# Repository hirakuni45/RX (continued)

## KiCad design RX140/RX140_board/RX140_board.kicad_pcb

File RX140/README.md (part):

## RX140 features / 特徴

- RXv2 core / RXv2 コア
- Maximum operating frequency 48MHz / 最大動作周波数 48MHz
- Single-precision 32-bit floating point / 32 ビット単精度浮動小数点
- 1.8V ～ 5.5V Operation / 動作
- RSCAN CAN Module / RSCAN CAN モジュール
- 12 Bits A/D / １２ビットＡ／Ｄ変換器
- 8 Bits D/A / ８ビットＤ／Ａ変換器

### Package/パッケージ

|R5F5140---XX|Package/パッケージ|Pin/ピン数|Pitch/ピッチ|
|---|:-:|:-:|:-:|
|R5F5140xxxFN|LFQFP|80|0.50|
|R5F5140xxxFM|LFQFP|64|0.50|
|R5F5140xxxFK|LQFP|64|0.80|
|R5F5140xxxFL|LFQFP|48|0.50|
|R5F5140xxxNE|HWQFN|48|0.50|
|R5F5140xxxFJ|LFQFP|32|0.80|
|R5F5140xxxNH|HWQFN|32|0.50|

### Ambient operating temperature/動作周囲温度

|R5F5140--X--|degree Celsius|
|---|:-:|
|R5F5140xxDxx|-40 ～ +85℃|
|R5F5140xxGxx|-40 ～ +105℃|

### Crypt/暗号

|R5F5140-X---|Crypt|
|---|:-:|
|R5F5140xAxxx|-|
|R5F5140xBxxx|〇|

### Memoey size/メモリ容量

|R5F5140X----|CodeFlash|RAM|DataFlash|
|---|:-:|:-:|:-:|
|R5F51406xxxx|256K|64K|8K|
|R5F51405xxxx|128K|32K|8K|
|R5F51403xxxx|64K|16K|4K|

### Data Flash/データ・フラッシュ

|Capacity|Erase Size|Blank Check Size|Write Size|Erase Value|ID|
|:-:|:-:|:-:|:-:|:-:|:-:|
|4K/8K|256|1/256|1|0xFF|4|

---

## RX140 Linker file / リンカーファイル

|Type|Code Flash|RAM|Data Flash|Linker File|Ustack|Istack|
|---|:-:|:-:|:-:|---|:-:|:-:|
|R5F51406|256K|64K|8K|[R5F51406.ld](R5F51406.ld?ts=4)|3072|1024|
|R5F51405|128K|32K|8K|[R5F51405.ld](R5F51405.ld?ts=4)|1536|512|
|R5F51403|64K|16K|4K|[R5F51403.ld](R5F51403.ld?ts=4)|768|256|

---

## RX140 Dedicated class / 専用クラス

|Function/機能|Source|Remarks/備考|
|---|---|:-:|
|Peripheral Name/ペリフェラル名|[peripheral.hpp](peripheral.hpp?ts=4)||
|Hardware-specific Definition/ハード固有定義|[board_profile.hpp](board_profile.hpp?ts=4)||
|Operating Frequency Definition/動作周波数定義|[clock_profile.hpp](clock_profile.hpp?ts=4)||
|Power Control/電力制御|[power_mgr.hpp](power_mgr.hpp?ts=4)||
|Port Definition/ポート定義|[port.hpp](port.hpp?ts=4)||
|Interrupt Definition/割り込み定義|[icu.hpp](icu.hpp?ts=4)||
|Interrupt Management/割り込み管理|[icu_mgr.hpp](icu_mgr.hpp?ts=4)||
|Port Function Definition/ポート機能定義|[mpc.hpp](mpc.hpp?ts=4)||
|Port Mapping/ポートマッピング|[port_map.hpp](port_map.hpp?ts=4)||
|Port Mapping IRQ/ポートマッピング IRQ|[port_map_irq.hpp](port_map_irq.hpp?ts=4)||
|Port Mapping MTU/ポートマッピング MTU|[port_map_mtu.hpp](port_map_mtu.hpp?ts=4)||
|Port Mapping MTU/ポートマッピング TMR|[port_map_tmr.hpp](port_map_tmr.hpp?ts=4)||
|A/D Definition/A/D 定義|[RX231/s12ade.hpp](../RX231/s12ade.hpp?ts=4)||
|D/A Definition/D/A 定義|[da.hpp](da.hpp?ts=4)||
|BUS Definition/BUS 定義|[bus.hpp](bus.hpp?ts=4)||
|ELC Definition/ELC 定義|[elc.hpp](elc.hpp?ts=4)||
|RTC Definition/RTC 定義|[rtc.hpp](rtc.hpp?ts=4)||
|FLASH Definition/FLASH 定義|[flash.hpp](flash.hpp?ts=4)||
|FLASH I/O Definition/FLASH I/O 定義|[RX24T/flash_io.hpp](../RX24T/flash.hpp?ts=4)||
|System Definition/システム定義|[system.hpp](system.hpp?ts=4)||
|System I/O Definition/システム I/O 定義|[system_io.hpp](system_io.hpp?ts=4)||
|A/D I/O Definition/A/D I/O 定義|[RX24T/adc_io.hpp](../RX24T/adc_io.hpp?ts=4)||
|D/A out Definition/D/A out 定義|[RX600/dac_out.hpp](../RX600/adc_io.hpp?ts=4)||

---

## Basic Pin Assignments / 基本ピンアサイン

|Terminal/端子|LFQFP 64|LFQFP 80|
|---|---|---|
|VCL|VCL(2)|VCL(4)|
|Reset Input/リセット入力|RES#(6)|RES#(9)|
|Mode Controle/モード制御|MD/FINED(3)|MD/FINED(6)|
|RXD|P30/RXD1(14)|P30/RXD1(18)|
|TXD|P26/TXD1(16)|P26/TXD1(20)|
|Power/電源|VCC(10), VCC(38)|VCC(13), VCC(48)|
|GND/接地|VSS(8), VSS(40)|VSS(11), VSS(50)|
|Analog Power/アナログ電源|AVCC0(62)|AVCC0(77)|
|Analog GND/アナログ接地|AVSS0(64)|AVSS0(79)|
|Analog Refarence L/アナログ基準電源Ｌ|VREFL0(59)|VREFL0(74)|
|Analog Refarence H/アナログ基準電源Ｈ|VREFH0(61)|VREFH0(76)|
|OSC out|XTAL(7)|XTAL(10)|
|OSC in|EXTAL(9)|EXTAL(12)|
|Sub OSC out|XCOUT(5)|XCOUT(8)|
|Sub OSC in|XCIN(4)|XCIN(7)|

- VCL: 4.7uF/25V

|Mode/モード|MD|
|---|:---:|
|Serial BOOT/シリアルブート|0|
|Single Chip/シングルチップ|1|

---

## Peripheral / ペリフェラル

- [peripheral.hpp](peripheral.hpp?ts=4)

|Peripheral|Function|機能|
|---|---|---|
|CAC|Clock Frequency Accuracy Measurement Circuit|クロック周波数精度測定回路|
|DTC|Data Transfer Controller|データトランスファコントローラ|
|ELC|Event Link Controller|イベントリンクコントローラ|
|MTU0|Multi-Function Timer Pulse Unit 0|マルチファンクションタイマパルスユニット０|
|MTU1|Multi-Function Timer Pulse Unit 1|マルチファンクションタイマパルスユニット１|
|MTU2|Multi-Function Timer Pulse Unit 2|マルチファンクションタイマパルスユニット２|
|MTU3|Multi-Function Timer Pulse Unit 3|マルチファンクションタイマパルスユニット３|
|MTU4|Multi-Function Timer Pulse Unit 4|マルチファンクションタイマパルスユニット４|
|MTU5|Multi-Function Timer Pulse Unit 5|マルチファンクションタイマパルスユニット５|
|POE2|Port Output Enable 2|ポートアウトプットイネーブル２|
|TPU0|16-Bit Timer Pulse Unit 0|16 ビットタイマパルスユニット０|
|TPU1|16-Bit Timer Pulse Unit 1|16 ビットタイマパルスユニット１|
|TPU2|16-Bit Timer Pulse Unit 2|16 ビットタイマパルスユニット２|
|TPU3|16-Bit Timer Pulse Unit 3|16 ビットタイマパルスユニット３|
|TPU4|16-Bit Timer Pulse Unit 4|16 ビットタイマパルスユニット４|
|TPU5|16-Bit Timer Pulse Unit 5|16 ビットタイマパルスユニット５|
|TMR0|8-Bit Timer 0|8 ビットタイマ０|
|TMR1|8-Bit Timer 1|8 ビットタイマ１|
|TMR2|8-Bit Timer 2|8 ビットタイマ２|
|TMR3|8-Bit Timer 3|8 ビットタイマ３|
|CMT0|Compare Match Timer 0|コンペアマッチタイマ０|
|CMT1|Compare Match Timer 1|コンペアマッチタイマ１|
|RTC|Realtime Clock|リアルタイムクロック|
|LPT|Low Power Timer|ローパワータイマ|
|IWDT|Independent Watchdog Timer|独立ウォッチドッグタイマ|
|SCI1|Serial Communications Interface 1|シリアルコミュニケーションインタフェース１|
|SCI5|Serial Communications Interface 5|シリアルコミュニケーションインタフェース５|
|SCI6|Serial Communications Interface 6|シリアルコミュニケーションインタフェース６|
|SCI8|Serial Communications Interface 8|シリアルコミュニケーションインタフェース８|
|SCI9|Serial Communications Interface 9|シリアルコミュニケーションインタフェース９|
|SCI11|Serial Communications Interface 11|シリアルコミュニケーションインタフェース１１|
|SCI12|Serial Communications Interface 12|シリアルコミュニケーションインタフェース１２|
|RIIC0|I2C-bus Interface 0|I2C バスインタフェース０|
|RSCAN|RSCAN Module|RSCAN モジュール|
|RSPI0|Serial Peripheral Interface 0|シリアルペリフェラルインタフェース０|
|CRC|CRC Calculator|CRC 演算器|
|CTSU|Capacitive Touch Sensing Unit|静電容量式タッチセンサ|
|S12AD|12-Bit A/D Converter|12 ビット A/D コンバータ|
|DA|8-Bit D/A Converter|8 ビット D/A コンバータ|
|CMPB|Comparator B|コンパレータＢ|
|DOC|Data Operation Circuit|データ演算回路|

---

## Port map order (IRQ) / ポートマップ候補 (IRQ)

- [port_map_irq.hpp](port_map_irq.hpp?ts=4)

### LFQFP48

|IRQ|FIRST|SECOND|THIRD|FOURTH|
|---|---|---|---|---|
|IRQ0|P30 (10)|PD0 (--)|PH1 (19)|-|
|IRQ1|P31 (9)|PD1 (--)|PH2 (18)|-|
|IRQ2|P12 (--)|P32 (--)|P36 (6)|PD2 (--)|
|IRQ3|P13 (--)|-|-|-|
|IRQ4|P14 (16)|P34 (--)|P37 (4)|PB1 (27)|
|IRQ5|P15 (15)|PA4 (32)|PE5 (--)|-|
|IRQ6|P16 (14)|PA3 (33)|-|-|
|IRQ7|P17 (13)|PE2 (37)|-|-|

### LFQFP64

|IRQ|FIRST|SECOND|THIRD|FOURTH|
|---|---|---|---|---|
|IRQ0|P30 (14)|PD0 (--)|PH1 (23)|-|
|IRQ1|P31 (13)|PD1 (--)|PH2 (22)|-|
|IRQ2|P12 (--)|P32 (12)|P36 (9)|PD2 (--)|
|IRQ3|P13 (--)|-|-|-|
|IRQ4|P14 (20)|P34 (--)|P37 (7)|PB1 (37)|
|IRQ5|P15 (19)|PA4 (42)|PE5 (46)|-|
|IRQ6|P16 (18)|PA3 (43)|-|-|
|IRQ7|P17 (17)|PE2 (49)|-|-|

### LFQFP80

|IRQ|FIRST|SECOND|THIRD|FOURTH|
|---|---|---|---|---|
|IRQ0|P30 (18)|PD0 (66)|PH1 (31)|-|
|IRQ1|P31 (17)|PD1 (65)|PH2 (30)|-|
|IRQ2|P12 (28)|P32 (16)|P36 (12)|PD2 (64)|
|IRQ3|P13 (27)|-|-|-|
|IRQ4|P14 (26)|P34 (15)|P37 (10)|PB1 (47)|
|IRQ5|P15 (25)|PA4 (53)|PE5 (58)|-|
|IRQ6|P16 (24)|PA3 (54)|-|-|
|IRQ7|P17 (23)|PE2 (61)|-|-|

---

## Port map order / ポートマップ候補

- [port_map.hpp](port_map.hpp?ts=4)

### LFQFP48

|Peripheral|FIRST|SECOND|THIRD|
|---|---|---|---|
|SCI1 / RXD|P15 (15)|P30 (10)|-|
|SCI1 / TXD|P16 (14)|P26 (12)|-|
|SCI1 / SCK|P17 (13)|P27 (11)|-|
|SCI5 / RXD|PA2 (--)|PA3 (33)|PC2 (26)|
|SCI5 / TXD|PA4 (32)|PA4 (32)|PC3 (25)|
|SCI5 / SCK|PA1 (34)|PA1 (34)|PC4 (24)|
|SCI6 / RXD|PB0 (29)|PD1 (--)|-|
|SCI6 / TXD|PB1 (27)|PD0 (--)|-|
|SCI6 / SCK|PB3 (26)|PD2 (--)|-|
|SCI8 / RXD|PC6 (22)|-|-|
|SCI8 / TXD|PC7 (21)|-|-|
|SCI8 / SCK|PC5 (23)|-|-|
|SCI9 / RXD|PB6 (--)|-|-|
|SCI9 / TXD|PB7 (--)|-|-|
|SCI9 / SCK|PB5 (25)|-|-|
|SCI12 / RXD|PE2 (37)|-|-|
|SCI12 / TXD|PE1 (38)|-|-|
|SCI12 / SCK|PE0 (--)|-|-|
|RIIC0 / SCL|P16 (14)|P12 (--)|-|
|RIIC0 / SDA|P17 (13)|P13 (--)|-|
|RSCAN / CRX|P15 (15)|P55 (--)|-|
|RSCAN / CTX|P14 (16)|P54 (--)|-|
|RSPI0 / RSPCK|PA5 (--)|PB0 (29)|PC5 (23)|
|RSPI0 / MOSI|PA6 (31)|P16 (14)|PC6 (22)|
|RSPI0 / MISO|PA7 (21)|P17 (13)|PC7 (21)|
|RSPI0 / SSL0|PA4 (32)|PC4 (24)|-|
|RSPI0 / SSL1|PA0 (--)|-|-|
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
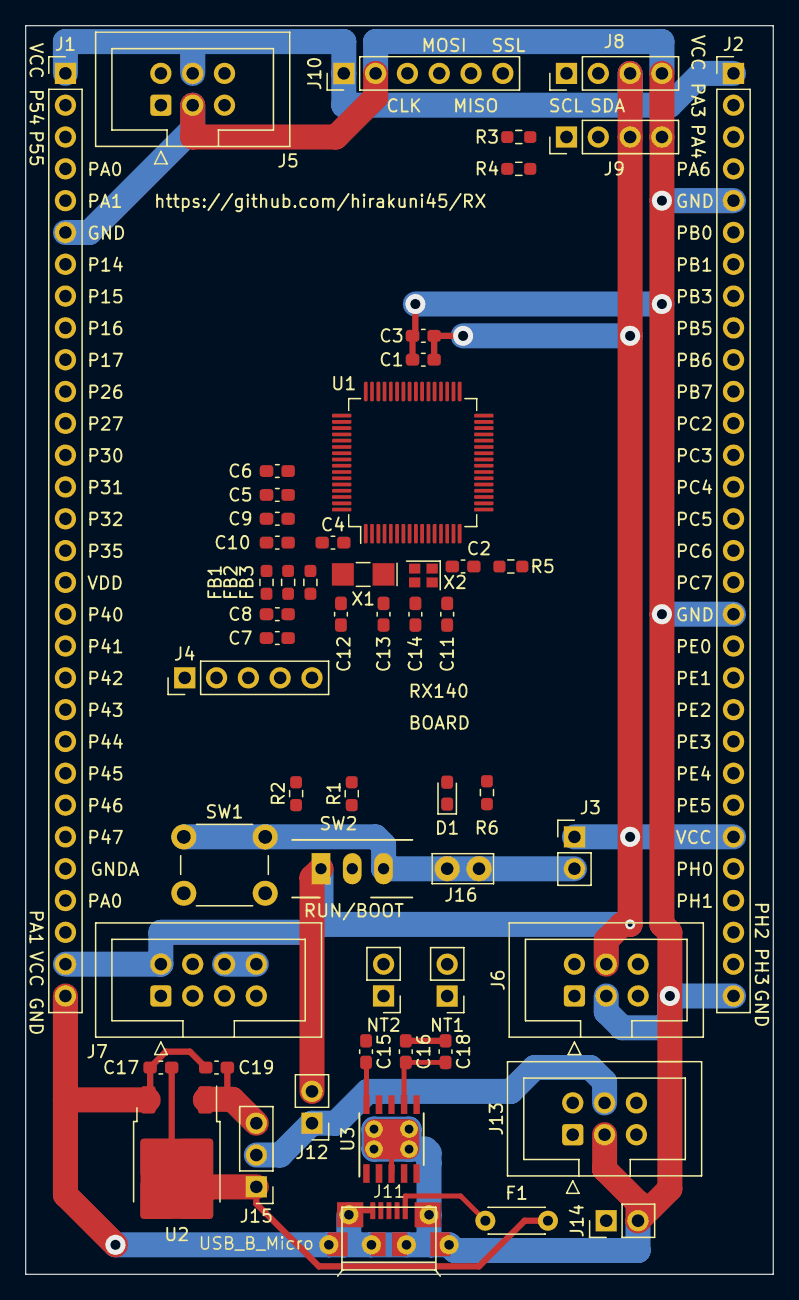
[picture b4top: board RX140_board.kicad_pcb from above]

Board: 2 copper layers, 59.7 x 99.7 mm, 55 parts (0 on the bottom side), 75 nets.

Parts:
C1, C2, C6, C7, C10, C15, C17, C18: 0.1uF; C_0603_1608Metric_Pad1.08x0.95mm_HandSolder
C3, C8, C16: 10uF; C_0603_1608Metric_Pad1.08x0.95mm_HandSolder
C4: 4.7uF; C_0603_1608Metric_Pad1.08x0.95mm_HandSolder
C5, C9: 0.01uF; C_0603_1608Metric_Pad1.08x0.95mm_HandSolder
C11, C14: 5pF; C_0603_1608Metric_Pad1.08x0.95mm_HandSolder
C12, C13: 10pF; C_0603_1608Metric_Pad1.08x0.95mm_HandSolder
C19: 1uF; C_0603_1608Metric_Pad1.08x0.95mm_HandSolder
D1: LED; LED_0603_1608Metric_Pad1.05x0.95mm_HandSolder
F1: MF-R050; C_Disc_D4.3mm_W1.9mm_P5.00mm
FB1, FB2, FB3: FB; R_0603_1608Metric_Pad0.98x0.95mm_HandSolder
J1: PIN-A; PinHeader_1x30_P2.54mm_Vertical
J2: PIN-B; PinHeader_1x30_P2.54mm_Vertical
J3: POWER; PinHeader_1x02_P2.54mm_Vertical
J4: D/A; PinHeader_1x05_P2.54mm_Vertical
J5: SCI12; IDC-Header_2x03_P2.54mm_Vertical
J6: SCI1; IDC-Header_2x03_P2.54mm_Vertical
J7: EMU; IDC-Header_2x04_P2.54mm_Vertical
J8: I2C-A; PinHeader_1x04_P2.54mm_Vertical
J9: I2C-B; PinHeader_1x04_P2.54mm_Vertical
J10: RSPI; PinHeader_1x06_P2.54mm_Vertical
J11: USB_B_Micro; USB_MICRO_B-HIROSE-ZX62R-B-5P
J12: 3.3V_CON; PinHeader_1x02_P2.54mm_Vertical
J13: Serial; IDC-Header_2x03_P2.54mm_Vertical
J14: /DTR; PinHeader_1x02_P2.54mm_Vertical
J15: 5/3.3; PinHeader_1x03_P2.54mm_Vertical
J16: GND; TestPoint_Bridge_Pitch2.54mm_Drill1.0mm
NT1: TIE_RXD; PinHeader_1x02_P2.54mm_Vertical
NT2: TIE_TXD; PinHeader_1x02_P2.54mm_Vertical
R1, R2, R5: 10K; R_0603_1608Metric_Pad0.98x0.95mm_HandSolder
R3, R4: 2K; R_0603_1608Metric_Pad0.98x0.95mm_HandSolder
R6: 1.5K; R_0603_1608Metric_Pad0.98x0.95mm_HandSolder
SW1: RES; SW_PUSH_6mm
SW2: RUN/BOOT; SW_3P_SPDT_Angled
U1: RX140; LQFP-64_10x10mm_P0.5mm
U2: NJU7223DL1-33; TO-252-2
U3: CH340K; SSOP-10_3.9x4.9mm_P1.00mm
X1: 32.768KHz; Crystal_SMD_EuroQuartz_EQ161-2Pin_3.2x1.5mm_HandSoldering
X2: 12MHz; Crystal_SMD_2016-4Pin_2.0x1.6mm

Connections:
/CH340 Serial USB/RXD: J13.1, NT2.1, U3.9 (RXD)
/CH340 Serial USB/TXD: J13.2, NT1.1, U3.8 (TXD)
DA0: J1.27, J4.2, U1.1 (P03)
DA1: J1.28, J4.3, U1.63 (P05)
GND: C1.1, C2.1, C3.2, C4.1, C7.1, C8.1, C11.1, C12.1, C13.1, C14.1, C15.1, C16.1, C17.1, C18.1, C19.1, FB1.1, J1.6, J1.30, J2.5, J2.18, J2.30, J3.2, J5.3, J6.3, J7.6, J7.8, J8.4, J9.4, J10.2, J11.5 (GND), J11.6 (Shield), J13.3, J14.2, J16.1, SW1.1, SW2.3, U1.8 (VSS), U1.40 (VSS), U2.3 (GND), U3.0 (GND), U3.3 (GND), X2.2, X2.4
GNDA: C5.2, C6.2, C9.1, C10.1, FB1.2, J1.26, J4.4, J4.5, U1.59 (VREFL0/PJ7), U1.64 (AVSS0)
LED: J1.8, R6.1, U1.19 (P15)
MISOA: J2.17, J10.5, U1.27 (PC7)
MOSIA: J2.16, J10.4, U1.28 (PC6)
NMI: J1.16, R5.1, U1.11 (P35)
unnamed: D1.1 (K), R6.2
unnamed: J7.1, R2.1, SW1.2, U1.6 (~RES)
unnamed: J7.3, R1.2, U1.3 (PG7/MD)
unnamed: J11.3 (D+), U3.1 (UD+)
unnamed: J11.2 (D-), U3.2 (UD-)
unnamed: F1.1, J11.1 (VBUS)
unnamed: J12.1, J13.4, J15.2
unnamed: J13.5, U3.6 (RTS#)
unnamed: J13.6, U3.5 (CTS#)
unnamed: J14.1, U3.4 (DTR#)
unnamed: C16.2, C17.2, C18.2, F1.2, J15.1, U2.2 (Vin), U3.7 (VCC)
unnamed: C19.2, J15.3, U2.1 (Vout)
unnamed: R1.1, SW2.2
unnamed: C11.2, U1.9 (P36/EXTAL), X2.1
unnamed: C14.2, U1.7 (P37/XTAL), X2.3
unnamed: C13.2, U1.5 (PH6/XCOUT), X1.1
unnamed: C12.2, U1.4 (PH7/XCIN), X1.2
unnamed: C4.2, U1.2 (VCL)
unnamed: C9.2, C10.2, FB3.1, U1.61 (VREFH0/PJ6)
unnamed: C15.2, U3.10 (V3)
P27: J1.12, U1.15 (P27)
P32: J1.15, U1.12 (P32)
P40: J1.18, U1.60 (P40)
P41: J1.19, U1.58 (P41)
P42: J1.20, U1.57 (P42)
P43: J1.21, U1.56 (P43)
P44: J1.22, U1.55 (P44)
P45: J1.23, U1.54 (P45)
P46: J1.24, U1.53 (P46)
P47: J1.25, U1.52 (P47)
P54: J1.2, U1.26 (P54)
P55: J1.3, U1.25 (P55)
PA0: J1.4, U1.45 (PA0)
PA1: J1.5, U1.44 (PA1)
PA3: J2.2, U1.43 (PA3)
PA4: J2.3, U1.42 (PA4)
PA6: J2.4, U1.41 (PA6)
PB0: J2.6, U1.39 (PB0)
PB1: J2.7, U1.37 (PB1)
PB3: J2.8, U1.36 (PB3)
PB5: J2.9, U1.35 (PB5)
PB6: J2.10, U1.34 (PB6/PC0)
PB7: J2.11, U1.33 (PB7/PC1)
PC2: J2.12, U1.32 (PC2)
PC3: J2.13, U1.31 (PC3)
PE0: J2.19, J5.6, U1.51 (PE0)
PE4: J2.23, U1.47 (PE4)
PE5: J2.24, U1.46 (PE5)
PH0: J2.26, U1.24 (PH0)
PH1: J2.27, U1.23 (PH1)
PH2: J2.28, U1.22 (PH2)
PH3: J2.29, U1.21 (PH3)
RSPCKA: J2.15, J10.3, U1.29 (PC5)
RXD1: J1.13, J6.2, J7.5, NT1.2, U1.14 (P30)
RXD12: J2.21, J5.2, U1.49 (PE2)
SCL0: J1.9, J8.1, J9.1, R3.2, U1.18 (P16)
SDA0: J1.10, J8.2, J9.2, R4.2, U1.17
SSLA0: J2.14, J10.6, U1.30 (PC4)
TXD1: J1.11, J6.1, J7.7, NT2.2, U1.16 (P26)
TXD12: J2.20, J5.1, U1.50 (PE1)
VCC: C1.2, C2.2, C3.1, C7.2, C8.2, D1.2 (A), FB2.2, FB3.2, J1.1, J1.29, J2.1, J2.25, J3.1, J5.4, J6.4, J7.2, J8.3, J9.3, J10.1, J12.2, R2.2, R3.1, R4.1, R5.2, SW2.1, U1.10 (VCC), U1.38 (VCC)
VDD: C5.1, C6.1, FB2.1, J1.17, J4.1, U1.62 (AVCC0)
/CTS1: J1.7, J6.5, U1.20 (P14)
/CTS12: J2.22, J5.5, U1.48 (PE3)
/RTS1: J1.14, J6.6, U1.13 (P31)

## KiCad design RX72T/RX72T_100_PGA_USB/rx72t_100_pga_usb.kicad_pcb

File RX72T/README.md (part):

## RX72T features / 特徴

- RXv3 core / RXv3 コア
- Maximum operating frequency 200MHz / 最大動作周波数 200MHz
- Single-precision 32-bit floating point / 32 ビット単精度浮動小数点
- 2.7V ～ 5.5V Operation / 動作
- USB2.0 Full Speed, Host, Function (Optional)
- CAN Module (CAN) / CAN モジュール (CAN)
- Arithmetic Unit for Trigonometric Functions (TFUv1) / 三角関数演算器 (TFUv1)
- 12 Bits A/D / １２ビットＡ／Ｄ変換器
- 12 Bits D/A / １２ビットＤ／Ａ変換器

### Package/パッケージ

|R5F572T---XX|Package/パッケージ|Pin/ピン数|Pitch/ピッチ|
|---|:-:|:-:|:-:|
|R5F572TxxxFB|LFQFP|144|0.50|
|R5F572TxxxFP|LFQFP|100|0.50|

### Ambient operating temperature/動作周囲温度

|R5F572T--X--|degree Celsius|
|---|:-:|
|R5F572TxxDxx|-40 ～ +85℃|
|R5F572TxxGxx|-40 ～ +105℃|

### PGA, TSIP, USB

|R5F572T-X---|PGA|TSIP|USB|
|---|:-:|:-:|:-:|
|R5F572TxAxxx|〇|-|-|
|R5F572TxBxxx|-|-|-|
|R5F572TxCxxx|〇|-|〇|
|R5F572TxExxx|〇|〇|-|
|R5F572TxFxxx|-|〇|-|
|R5F572TxGxxx|〇|〇|〇|

### Memoey size/メモリ容量

|R5F572TX----|CodeFlash|RAM|ECCRAM|DataFlash|
|---|:-:|:-:|:-:|:-:|
|R5F572TKxxxx|1M|128K|16K|32K|
|R5F572TFxxxx|512K|128K|16K|32K|

### Data Flash/データ・フラッシュ

|Capacity|Erase Size|Blank Check Size|Write Size|Erase Value|ID|
|:-:|:-:|:-:|:-:|:-:|:-:|
|32K|64|4/64|4|0x??|3|

---

## RX72T Linker file / リンカーファイル

|Type|Code Flash|RAM|Data Flash|Linker File|Ustack|Istack|
|---|:-:|:-:|:-:|---|:-:|:-:|
|R5F572TK|1024K|128K+16K|32K|[R5F572TK.ld](R5F572TK.ld?ts=4)|7168|1024|
|R5F572TF|512K|128K+16K|32K|[R5F572TF.ld](R5F572TF.ld?ts=4)|7168|1024|

RAM: 16K(With ECC)

---

## RX72T Dedicated class / 専用クラス

|Function/機能|Source|Remarks/備考|
|---|---|:-:|
|Peripheral Name/ペリフェラル名|[peripheral.hpp](peripheral.hpp?ts=4)||
|Hardware-specific Definition/ハード固有定義|[board_profile.hpp](board_profile.hpp?ts=4)||
|Operating Frequency Definition/動作周波数定義|[clock_profile.hpp](clock_profile.hpp?ts=4)||
|Power Control/電力制御|[power_mgr.hpp](power_mgr.hpp?ts=4)||
|Port Definition/ポート定義|[port.hpp](port.hpp?ts=4)||
|Interrupt Definition/割り込み定義|[icu.hpp](icu.hpp?ts=4)||
|Interrupt Management/割り込み管理|[icu_mgr.hpp](icu_mgr.hpp?ts=4)||
|Port Function Definition/ポート機能定義|[mpc.hpp](mpc.hpp?ts=4)||
|Port Mapping/ポートマッピング|[port_map.hpp](port_map.hpp?ts=4)||
|Port Mapping IRQ/ポートマッピング IRQ|[port_map_irq.hpp](port_map_irq.hpp?ts=4)||
|Port Mapping MTU/ポートマッピング MTU|[port_map_mtu.hpp](port_map_mtu.hpp?ts=4)||
|Port Mapping TMR/ポートマッピング TMR|[port_map_tmr.hpp](port_map_tmr.hpp?ts=4)||
|Port Mapping GPTW/ポートマッピング GPTW|[port_map_gptw.hpp](port_map_gptw.hpp?ts=4)||
|POE3 Definition/POE3 定義|[poe3.hpp](poe3.hpp?ts=4)||
|A/D Definition/A/D 定義|[s12adh.hpp](s12adh.hpp?ts=4)||

---

## Basic Pin Assignments / 基本ピンアサイン

|Terminal/端子|LFQFP 100|LFQFP 144|
|---|---|---|
|VCL|VCL(5)|VCL(10)|
|Reset Input/リセット入力|RES#(10)|RES#(15)|
|Mode Controle/モード制御|MD/FINED(6)|MD/FINED(11)|
|UB|P00/UB(4)|P00/UB(9)|
|EMLE|EMLE(2)|EMLE(7)|
|RXD|PD5/RXD1(20)|PD5/RXD1(25)|
|TXD|PD3/TXD1(22)|PD3/TXD1(27)|
|UPSEL|PE2/UPSEL(15)|PE2/UPSEL(20)|
|USB_VCC|VCC_USB(26)|VCC_USB(38)|
|USB_VSS|VSS_USB(31)|VSS_USB(37)|
|USB+|USB_DP(25)|USB_DP(36)|
|USB-|USB_DM(24)|USB_DM(35)|
|Power/電源|VCC(14), VCC(29), VCC(42), VCC(60)|VCC(6), VCC(19), VCC(42), VCC(64), VCC(88)|
|GND/接地|VSS(3), VSS(12), VSS(31), VSS(44), VSS(62)|VSS(8), VSS(17), VSS(44), VSS(66), VSS(90)|
|Analog Power/アナログ電源|AVCC0(93), AVCC1(92), AVCC2(72)|AVCC0(134), AVCC1(133), AVCC2(104), AVCC2(105)|
|Analog GND/アナログ接地|AVSS0(94), AVSS1(95), AVSS2(73)|AVSS0(135), AVSS1(136), AVSS2(106)|
|Gain GND/ゲイン接地|PGAVSS0(91), PGAVSS1(86)|PGAVSS0(132), PGAVSS1(124)|
|OSC in|EXTAL(13)|EXTAL(18)|
|OSC out|XTAL(11)|XTAL(16)|

- VCL: 0.47uF/25V

|Mode/モード|UB|MD|UPSEL|
|---|:---:|:---:|:---:|
|Serial BOOT/シリアルブート|0|0|-|
|USB Boot/USB ブート|1|0|0/1|
|Single Chip/シングルチップ|-|1|-|

- EMLE: 0

---

## Device, Renesas / デバイス、ルネサス

- [device.hpp (SIG_RX72T)](../common/device.hpp?ts=4)
- [renesas.hpp (SIG_RX72T)](../common/renesas.hpp?ts=4)

|name space|Device, Renesas|デバイス、ルネサス|
|---|---|---|
|[clock_profile](../RX72T/clock_profile?ts=4)|Clock Profile|クロック・プロファイル|
|[SYSTEM](../RX72T/system.hpp?ts=4)|Clock Generation Circuit|クロック発生回路|
|[power_mgr](../RX72T/power_mgr.hpp?ts=4)|Low Power Consumption|消費電力低減機能|
|[ICU](../RX72T/icu.hpp?ts=4)|Interrupt Controller|割り込みコントローラ|
|[icu_mgr](../RX72T/icu_mgr.hpp?ts=4)|ICU Manager|ICU マネージャー|
|[MPC](../RX72T/mpc.hpp?ts=4)|Multi-Function Pin Controller|マルチファンクションピンコントローラ|
|[PORTx](../RX72T/port.hpp?ts=4)|I/O Ports|I/O ポート|
|[port_map](../RX72T/port_map.hpp?ts=4)|Port Mapping|ポート・マッピング|
|[port_map_mtu](../RX72T/port_map_mtu.hpp?ts=4)|Port Mapping MTU|ポート・マッピング MTU|
|[port_map_gptw](../RX72T/port_map_gptw.hpp?ts=4)|Port Mapping GPTW|ポート・マッピング GPTW|
|[port_map_tmr](../RX72T/port_map_tmr.hpp?ts=4)|Port Mapping TMR|ポート・マッピング TMR|
|[port_map_irq](../RX72T/port_map_irq.hpp?ts=4)|Port Mapping IRQ|ポート・マッピング IRQ|
|[FLASH](../RX600/flash.hpp?ts=4)|Flash Memory|フラッシュメモリ|
|[SYSTEM_IO](../RX600/system_io.hpp?ts=4)|System In/Out (Clock Setting)|システム In/Out (クロック設定)|
|[FLASH_IO](../RX600/flash_io.hpp?ts=4)|Flash In/Out|フラッシュ In/Out|
|[adc_in](../RX600/adc_in.hpp?ts=4)|A/D Converter Input|A/D 変換入力|
|[dac_out](../RX600/dac_out.hpp?ts=4)|D/A Converter Output|D/A 変換出力|
|[board_profile](../RX72T/board_profile?ts=4)|Board Profile|ボード・プロファイル|

---

## Peripheral / ペリフェラル

- [peripheral.hpp](peripheral.hpp?ts=4)

|Peripheral|Function|機能|
|---|---|---|
|[CAC](../RX600/cac.hpp?ts=4)|Clock Frequency Accuracy Measurement Circuit|クロック周波数精度測定回路|
|[DMAC0](../RX600/dmac.hpp?ts=4)|DMA Controller channel 0|DMA コントローラ・チャネル０|
|[DMAC1](../RX600/dmac.hpp?ts=4)|DMA Controller channel 1|DMA コントローラ・チャネル１|
|[DMAC2](../RX600/dmac.hpp?ts=4)|DMA Controller channel 2|DMA コントローラ・チャネル２|
|[DMAC3](../RX600/dmac.hpp?ts=4)|DMA Controller channel 3|DMA コントローラ・チャネル３|
|[DMAC4](../RX600/dmac.hpp?ts=4)|DMA Controller channel 4|DMA コントローラ・チャネル４|
|[DMAC5](../RX600/dmac.hpp?ts=4)|DMA Controller channel 5|DMA コントローラ・チャネル５|
|[DMAC6](../RX600/dmac.hpp?ts=4)|DMA Controller channel 6|DMA コントローラ・チャネル６|
|[DMAC7](../RX600/dmac.hpp?ts=4)|DMA Controller channel 7|DMA コントローラ・チャネル７|
|[DTC](../RX600/dtc.hpp?ts=4)|Data Transfer Controller|データトランスファコントローラ|
|[ELC](../RX600/elc.hpp?ts=4)|Event Link Controller|イベントリンクコントローラ|
|[MTU0](../RX600/mtu3.hpp?ts=4)|Multi-Function Timer Pulse Unit 0|マルチファンクションタイマパルスユニット０|
|[MTU1](../RX600/mtu3.hpp?ts=4)|Multi-Function Timer Pulse Unit 1|マルチファンクションタイマパルスユニット１|
|[MTU2](../RX600/mtu3.hpp?ts=4)|Multi-Function Timer Pulse Unit 2|マルチファンクションタイマパルスユニット２|
|[MTU3](../RX600/mtu3.hpp?ts=4)|Multi-Function Timer Pulse Unit 3|マルチファンクションタイマパルスユニット３|
|[MTU4](../RX600/mtu3.hpp?ts=4)|Multi-Function Timer Pulse Unit 4|マルチファンクションタイマパルスユニット４|
|[MTU5](../RX600/mtu3.hpp?ts=4)|Multi-Function Timer Pulse Unit 5|マルチファンクションタイマパルスユニット５|
|[MTU6](../RX600/mtu3.hpp?ts=4)|Multi-Function Timer Pulse Unit 6|マルチファンクションタイマパルスユニット６|
|[MTU7](../RX600/mtu3.hpp?ts=4)|Multi-Function Timer Pulse Unit 7|マルチファンクションタイマパルスユニット７|
|[MTU9](../RX600/mtu3.hpp?ts=4)|Multi-Function Timer Pulse Unit 9|マルチファンクションタイマパルスユニット９|
|[POE3](../RX72T/poe3.hpp?ts=4)|Port Output Enable 3|ポートアウトプットイネーブル３|
|[GPTW0](../RX600/gptw.hpp?ts=4)|General PWM Timer 0|汎用 PWM タイマ０|
|[GPTW1](../RX600/gptw.hpp?ts=4)|General PWM Timer 1|汎用 PWM タイマ１|
|[GPTW2](../RX600/gptw.hpp?ts=4)|General PWM Timer 2|汎用 PWM タイマ２|
|[GPTW3](../RX600/gptw.hpp?ts=4)|General PWM Timer 3|汎用 PWM タイマ３|
|[GPTW4](../RX600/gptw.hpp?ts=4)|General PWM Timer 4|汎用 PWM タイマ４|
|[GPTW5](../RX600/gptw.hpp?ts=4)|General PWM Timer 5|汎用 PWM タイマ５|
|[GPTW6](../RX600/gptw.hpp?ts=4)|General PWM Timer 6|汎用 PWM タイマ６|
|[GPTW7](../RX600/gptw.hpp?ts=4)|General PWM Timer 7|汎用 PWM タイマ７|
|[GPTW8](../RX600/gptw.hpp?ts=4)|General PWM Timer 8|汎用 PWM タイマ８|
|[GPTW9](../RX600/gptw.hpp?ts=4)|General PWM Timer 9|汎用 PWM タイマ９|
|[HRPWM](../RX600/hrpwm.hpp?ts=4)|High Resolution PWM Waveform Generation Circuit|高分解能 PWM 波形生成回路|
|[TMR0](../RX600/tmr.hpp?ts=4)|8-Bit Timer 0|8 ビットタイマ０|
|[TMR1](../RX600/tmr.hpp?ts=4)|8-Bit Timer 1|8 ビットタイマ１|
|[TMR2](../RX600/tmr.hpp?ts=4)|8-Bit Timer 2|8 ビットタイマ２|
|[TMR3](../RX600/tmr.hpp?ts=4)|8-Bit Timer 3|8 ビットタイマ３|
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
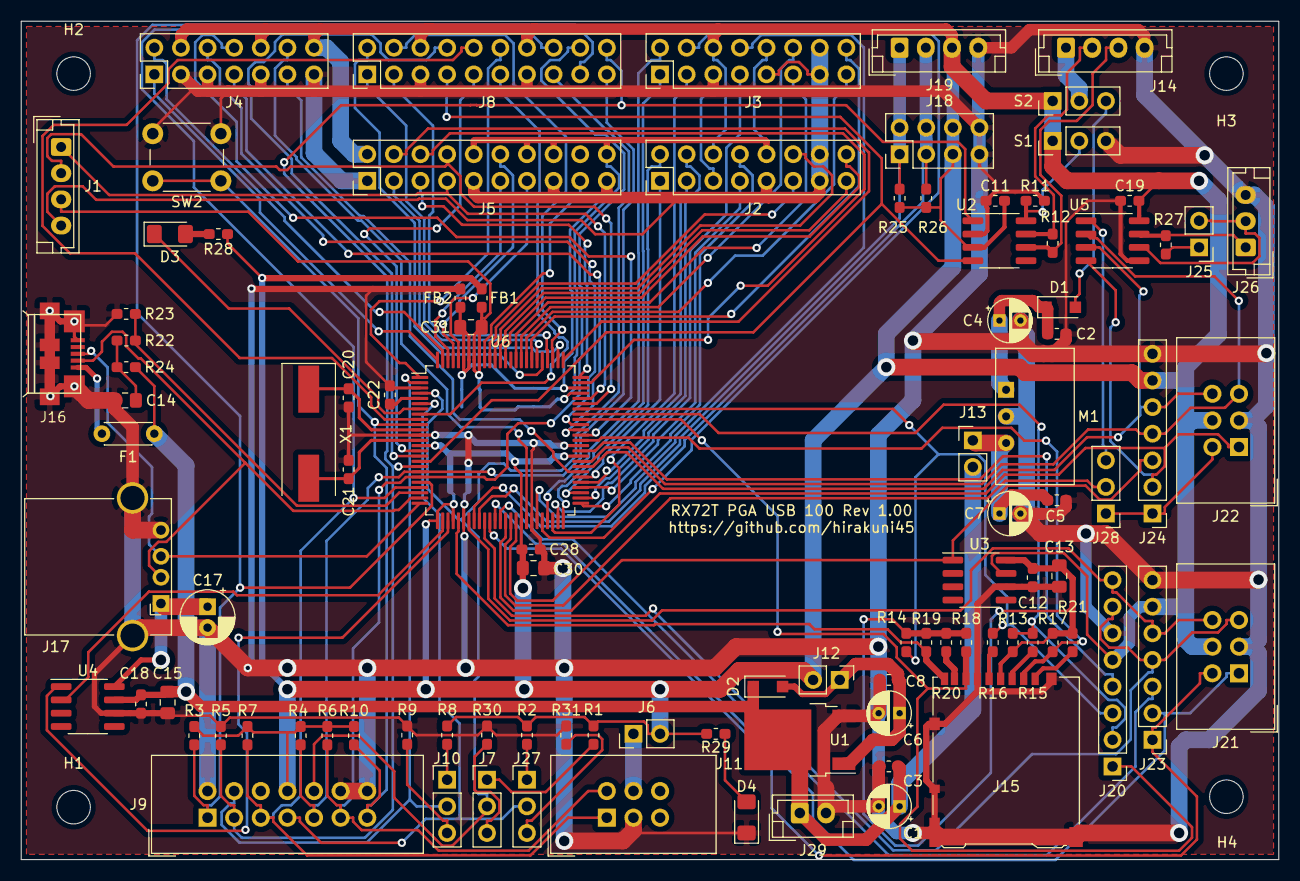
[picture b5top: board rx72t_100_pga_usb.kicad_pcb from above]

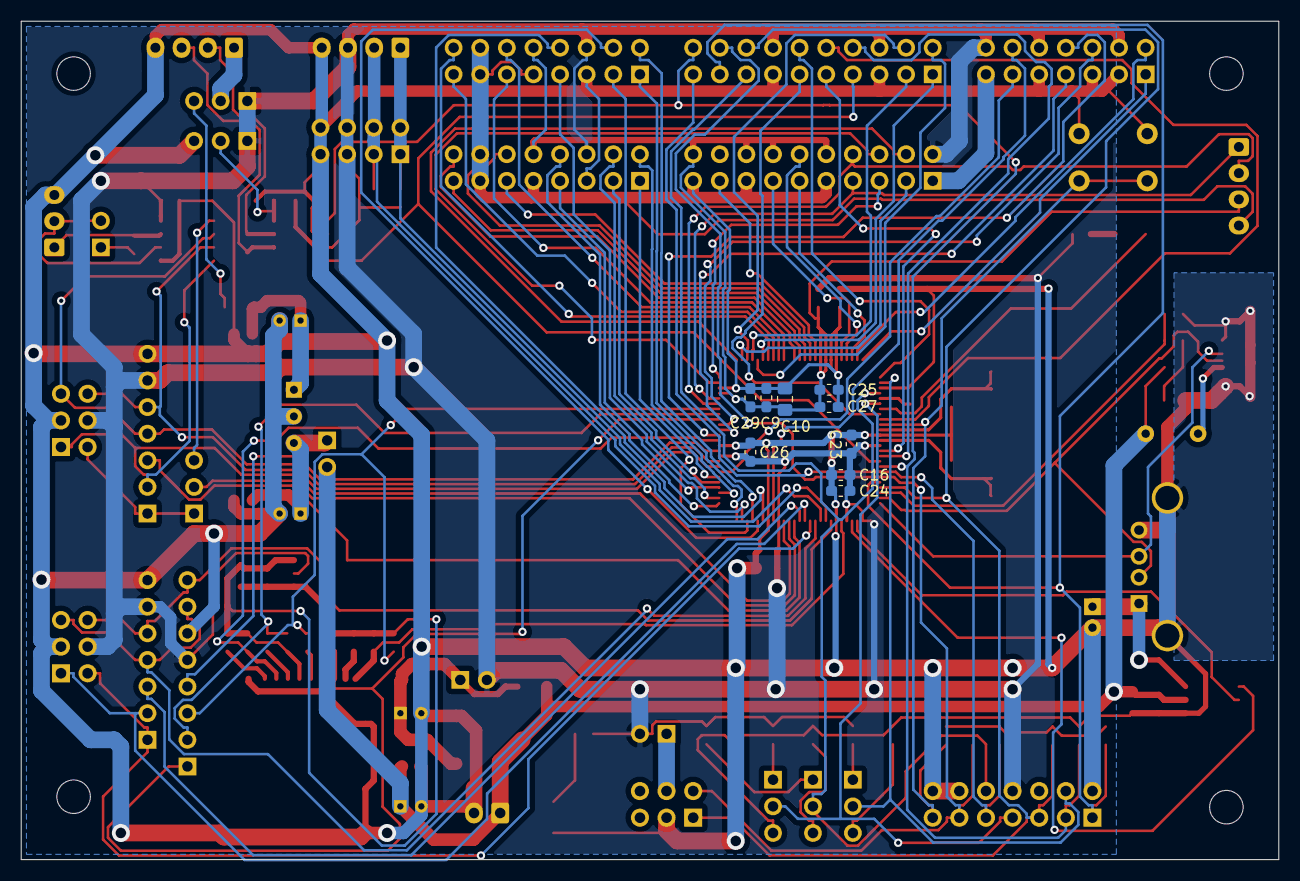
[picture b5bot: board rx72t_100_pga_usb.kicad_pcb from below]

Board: 2 copper layers, 120.0 x 80.0 mm, 113 parts (9 on the bottom side), 118 nets.

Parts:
C1, C6: 47uF; CP_Radial_D4.0mm_P2.00mm
C2, C5, C11, C12, C16, C18, C19: 0.1uF; C_0603_1608Metric_Pad1.05x0.95mm_HandSolder
C3, C8, C9, C22: 0.47uF; C_0603_1608Metric_Pad1.05x0.95mm_HandSolder
C4, C7: 10uF; CP_Radial_D4.0mm_P2.00mm
C10, C13: 10uF; C_0805_2012Metric_Pad1.15x1.40mm_HandSolder
C14, C15: 1uF; C_0805_2012Metric_Pad1.15x1.40mm_HandSolder
C17: 100uF; CP_Radial_D5.0mm_P2.00mm
C20, C21: 8pF; C_0603_1608Metric_Pad1.05x0.95mm_HandSolder
C23, C24, C25, C26, C27, C28, C29: 104; C_0603_1608Metric_Pad1.05x0.95mm_HandSolder
C30, C31: 47uF; C_0805_2012Metric_Pad1.15x1.40mm_HandSolder
D1, D2: 1A; D_SOD-123F
D3: RED; LED_1206_3216Metric_Pad1.42x1.75mm_HandSolder
D4: BLUE; LED_1206_3216Metric_Pad1.42x1.75mm_HandSolder
F1: 0.5A; C_Disc_D4.3mm_W1.9mm_P5.00mm
FB1, FB2: FB; R_0603_1608Metric_Pad1.05x0.95mm_HandSolder
H1, H2, H3, H4: Hole; MountingHole_3.2mm_M3
J1: DA_OUT; JST_EH_B4B-EH-A_1x04_P2.50mm_Vertical
J2: GPTW_012; PinHeader_2x08_P2.54mm_Vertical
J3: GPTW_456; PinHeader_2x08_P2.54mm_Vertical
J4: EXT_DG0; PinHeader_2x07_P2.54mm_Vertical
J5: EXT_AN; PinHeader_2x10_P2.54mm_Vertical
J6: SCI1_POW; PinHeader_1x02_P2.54mm_Vertical
J7: UB; PinHeader_1x03_P2.54mm_Vertical
J8: EXT_DG1; PinHeader_2x10_P2.54mm_Vertical
J9: E1_E2_Lite; IDC-Header_2x07_P2.54mm_Vertical
J10: EMU_MODE; PinHeader_1x03_P2.54mm_Vertical
J11: SCI1; IDC-Header_2x03_P2.54mm_Vertical
J12: 5V_POW; PinHeader_1x02_P2.54mm_Vertical
J13: 12V_POW; PinHeader_1x02_P2.54mm_Vertical
J14: CAN; JST_EH_B4B-EH-A_1x04_P2.50mm_Vertical
J15: MSD_Hirose_DM3AT; microSD_HC_Hirose_DM3AT-SF-PEJM5
J16: SLAVE; HIROSE_MicroB_SMD
J17: MASTER; USB-4AF103BS
J18: I2C_B; PinHeader_2x04_P2.54mm_Vertical
J19: I2C_A; JST_EH_B4B-EH-A_1x04_P2.50mm_Vertical
J20: RSPI; PinHeader_1x08_P2.54mm_Vertical
J21: SCI8; IDC-Header_2x03_P2.54mm_Vertical
J22: SCI11; IDC-Header_2x03_P2.54mm_Vertical
J23: SPI8; PinHeader_1x07_P2.54mm_Vertical
J24: SPI11; PinHeader_1x07_P2.54mm_Vertical
J25: RS-485 TERM; PinHeader_1x02_P2.54mm_Vertical
J26: RS-485; JST_EH_B3B-EH-A_1x03_P2.50mm_Vertical
J27: MD; PinHeader_1x03_P2.54mm_Vertical
J28: SER/RS-485; PinHeader_1x03_P2.54mm_Vertical
J29: 5VIN; JST_EH_B2B-EH-A_1x02_P2.50mm_Vertical
M1: BP5293-5; BP5293
R1, R2, R3, R4, R5, R6, R7, R9, R10, R30, R31: 4.7K; R_0603_1608Metric_Pad1.05x0.95mm_HandSolder
R8, R25, R26: 1K; R_0603_1608Metric_Pad1.05x0.95mm_HandSolder
R11: 47K; R_0603_1608Metric_Pad1.05x0.95mm_HandSolder
R12, R27: 120; R_0603_1608Metric_Pad1.05x0.95mm_HandSolder
R13, R14, R17, R18, R19, R20, R21: 22K; R_0603_1608Metric_Pad1.05x0.95mm_HandSolder
R15, R16: 22; R_0603_1608Metric_Pad1.05x0.95mm_HandSolder
R22: 15K; R_0603_1608Metric_Pad1.05x0.95mm_HandSolder
R23: 30K; R_0603_1608Metric_Pad1.05x0.95mm_HandSolder
R24: 100; R_0603_1608Metric_Pad1.05x0.95mm_HandSolder
R28: 1.5K; R_0603_1608Metric_Pad1.05x0.95mm_HandSolder
R29: 330; R_0603_1608Metric_Pad1.05x0.95mm_HandSolder
S1: T-POW; PinHeader_1x03_P2.54mm_Vertical
S2: CAN-POW; PinHeader_1x03_P2.54mm_Vertical
SW2: RESET; SW_PUSH_6mm_H4.3mm
U1: NJU7223DL1-33; TO-252-2
U2: SN65HVD230; SOP-8_3.76x4.96mm_P1.27mm
U3, U4: MIC2026-1BM; SOP-8_3.76x4.96mm_P1.27mm
U5: MAX3485; SOP-8_3.76x4.96mm_P1.27mm
U6: RX72T_100_PGA_USB; LQFP-100_14x14mm_P0.5mm
X1: 16MHz; Crystal_SMD_HC49-SD

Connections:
+3.3VA: C9.2, C10.2, C25.2, C27.2, C29.2, C31.1, FB1.2, J1.3, J2.10, J3.10, J5.10, J5.14, J5.16, J5.20, U6.72, U6.92, U6.93
+3V3: C11.2, C16.2, C19.2, C23.2, C24.2, C26.2, C28.2, C30.1, FB1.1, J2.6, J3.6, J4.4, J4.10, J4.14, J5.2, J6.2, J8.6, J8.14, J9.8, J12.2, J18.5, J18.6, J19.3, J20.5, J21.4, J22.4, J23.6, J24.6, R1.2, R2.1, R3.1, R4.1, R6.2, R7.1, R8.2, R10.1, R25.1, R26.1, R28.1, R29.1, S1.1, S2.1, U2.3, U3.7, U5.8, U6.14, U6.26, U6.29, U6.42, U6.60
+5V: C1.1, C3.2, C15.2, C18.2, D2.1, F1.1, J13.2, J29.1, R24.2, U1.2, U4.7
+12V: D1.2, S2.3
/I2C_SPI_SCI/MISO: J15.7, J20.1, R18.2, U6.67
/I2C_SPI_SCI/MOSI: J20.2, R13.2, R15.1, U6.68
/I2C_SPI_SCI/P32: J22.5, J24.4, U5.2, U6.59
/I2C_SPI_SCI/P33: J22.6, J24.5, U5.3, U6.58
/I2C_SPI_SCI/PB0: J20.7, J21.5, J23.4, U6.35
/I2C_SPI_SCI/PB3: J20.8, J21.6, J23.5, U6.32
/JTAG_IF/EMLE: J9.4, J10.2, U6.2
/JTAG_IF/MD_FINED: J9.7, J27.2, U6.6
/JTAG_IF/RESn: J9.13, R10.2, SW2.1, U6.10
/P00: J7.2, J8.15, J9.10, U6.4
/P10: J4.1, U6.100
/P11: J4.2, U6.99
/P23: J4.6, U6.66
/P24: J4.7, U6.65
/P25: J4.8, U6.64
/P40: J2.11, U6.90
/P41: J2.12, U6.89
/P42: J2.15, U6.88
/P43: J2.16, U6.87
/P44: J3.11, U6.85
/P45: J3.12, U6.84
/P46: J3.15, U6.83
/P47: J3.16, U6.82
/P52: J8.1, U6.81
/P53: J8.2, U6.80
/P54: J8.3, U6.79
/P55: J8.4, U6.78
/P60: J5.3, U6.77
/P61: J5.4, U6.76
/P62: J5.5, U6.75
/P63: J5.6, U6.74
/P64: J1.1, J5.7, U6.71
/P65: J1.2, J5.8, U6.70
/P70: J4.11, U6.57
/P71: J2.1, U6.56
/P72: J2.3, U6.55
/P73: J2.7, U6.54
/P74: J2.2, U6.53
/P75: J2.4, U6.52
/P76: J2.8, U6.51
/P80: J5.11, U6.98
/P81: J5.12, U6.97
/P82: J5.13, U6.96
/P90: J3.1, U6.50
/P91: J3.3, U6.48
/P92: J3.7, U6.49
/P93: J3.2, U6.47
/P94: J3.4, U6.46
/P95: J3.8, U6.45
/P96: J4.12, U6.43
/PD3: J8.16, J9.5, J11.1, R7.2, U6.22
/PD4: J8.17, J9.1, R3.2, U6.21
/PD5: J8.18, J9.11, J11.2, R6.1, U6.20
/PD6: J8.19, J9.9, R4.2, U6.19
/PD7: J8.20, J9.3, R5.2, U2.1, U6.18
/PE0: J8.7, U2.4, U6.17
/PE1: J8.8, U6.16
/PE2: J8.9, U6.15
/PE3: J8.10, U6.9
/PE4: J8.11, U6.8
/PE5: J8.12, U6.1
/PH0: J5.17, U6.91
/RX72T/P20_RSPCK: J20.3, R14.2, R16.1, U6.69
/RX72T/P30_SSL0: J15.2, R17.2, U6.63
/RX72T/P31_SSL1: J20.4, U6.61
/RX72T/PA0_TXD11: J22.1, J24.2, U5.4, U6.41
/RX72T/PA1_RXD11: J28.2, U6.40
/RX72T/PA2_SCK11: J24.3, U3.1, U6.39
/RX72T/PA3_SCK8: J23.3, U6.38
/RX72T/PA4_TXD8: J21.1, J23.2, U6.37
/RX72T/PA5_RXD8: J21.2, J23.1, U6.36
/RX72T/PB1_SCL: J18.1, J18.2, J19.1, R25.2, U6.34
/RX72T/PB2_SDA: J18.3, J18.4, J19.2, R26.2, U6.33
/RX72T/PB5_USB_VBUSEN: U4.1, U6.28
/RX72T/PB6_USB_OVRCUR: U4.2, U6.27
/RX72T/PD2_USB_VBUS: R22.2, R23.1, U6.23
/RX72T/USB_DM: J16.2, J17.2, U6.24
/RX72T/USB_DP: J16.3, J17.3, U6.25
/SDC_IF/INS: J15.9, R19.2, U6.30
GND: C1.2, C2.1, C3.1, C4.2, C5.1, C6.2, C7.2, C8.1, C11.1, C12.1, C13.1, C14.1, C15.1, C16.1, C17.2, C18.1, C19.1, C20.1, C21.1, C22.1, C23.1, C24.1, C26.1, C28.1, C30.2, D4.1, FB2.1, J2.5, J3.5, J4.3, J4.5, J4.9, J4.13, J5.1, J8.5, J8.13, J9.2, J9.12, J9.14, J11.3, J14.4, J15.6, J15.10, J15.11, J16.5, J16.6, J17.4, J17.5, J18.7, J18.8, J19.4, J20.6, J21.3, J22.3, J23.7, J24.7, J26.3, J29.2, M1.2, R5.1, R9.2, R11.2, R23.2, R30.1, R31.1, S1.3, SW2.2, U1.3, U2.2, U3.6, U4.6, U5.5, U6.3, U6.12, U6.31, U6.44, U6.62
GNDA: C9.1, C10.1, C25.1, C27.1, C29.1, C31.2, FB2.2, J1.4, J2.9, J2.13, J2.14, J3.9, J3.13, J3.14, J5.9, J5.15, J5.19, U6.73, U6.94, U6.95
unnamed: C2.2, C4.1, D1.1, M1.1
unnamed: C5.2, C7.1, J13.1, M1.3
unnamed: C6.1, C8.2, D2.2, J12.1, U1.1
unnamed: C12.2, C13.2, J15.4, R13.1, R14.1, R17.1, R18.1, R19.1, R20.1, R21.1, U3.8
unnamed: C14.2, R22.1, R24.1
unnamed: C17.1, J17.1, U4.8
unnamed: C20.2, U6.11, X1.1
unnamed: C21.2, U6.13, X1.2
unnamed: C22.2, U6.5
unnamed: D3.1, U6.7
unnamed: D3.2, R28.2
unnamed: D4.2, R29.2
unnamed: F1.2, J16.1
unnamed: J7.1, R1.1
unnamed: J7.3, R30.2
unnamed: J10.1, R8.1
unnamed: J10.3, R9.1
unnamed: J6.1, J11.4
unnamed: J14.1, S2.2
unnamed: J14.2, R12.1, U2.7
unnamed: J14.3, R12.2, U2.6
unnamed: J15.1, R21.2
unnamed: J15.3, R15.2
unnamed: J15.5, R16.2
unnamed: J15.8, R20.2
unnamed: J22.2, J24.1, J28.1
unnamed: J25.1, R27.1
unnamed: J25.2, J26.2, U5.6
unnamed: J26.1, R27.2, U5.7
unnamed: J27.1, R2.2
unnamed: J27.3, R31.2
unnamed: J28.3, U5.1
unnamed: R11.1, S1.2, U2.8

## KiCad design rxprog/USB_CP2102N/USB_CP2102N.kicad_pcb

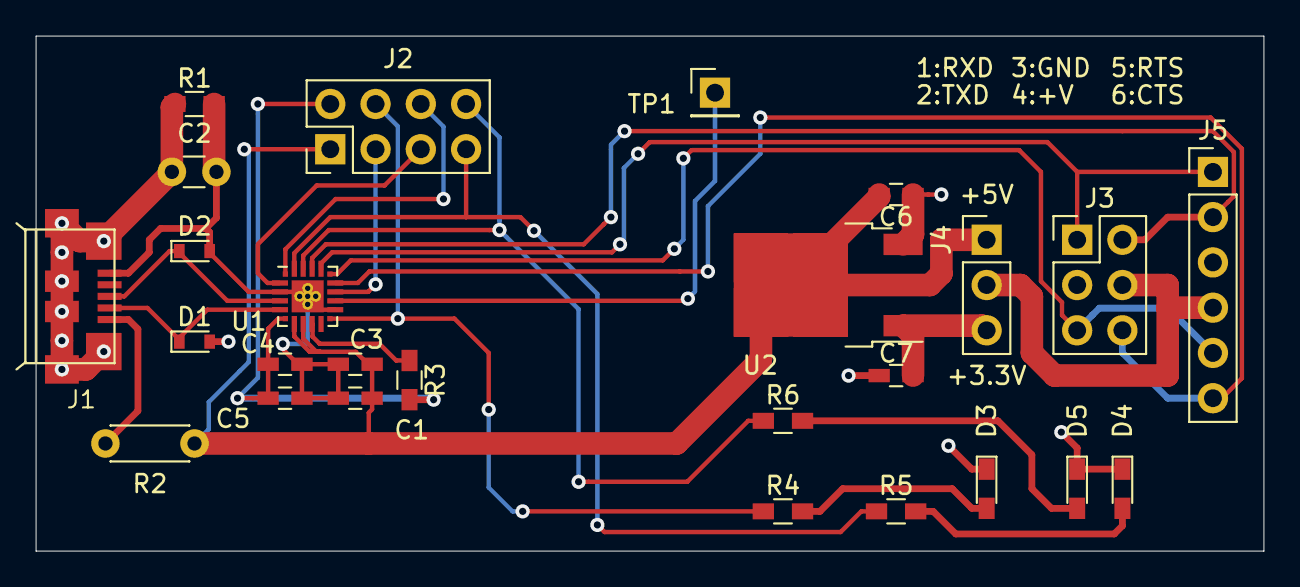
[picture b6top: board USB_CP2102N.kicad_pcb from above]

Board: 2 copper layers, 68.9 x 28.9 mm, 26 parts (0 on the bottom side), 24 nets.

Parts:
C1, C4, C6, C7: 0.1uF; C_0603_HandSoldering
C2: 100pF; C_Disc_D3.0mm_W1.6mm_P2.50mm
C3, C5: 4.7uF; C_0603_HandSoldering
D1, D2: 5.7V; D_0603
D3: Green; LED_0603_HandSoldering
D4: Red; LED_0603_HandSoldering
D5: Orange; LED_0603_HandSoldering
J1: USB_B_Micro; USB_MICRO_B-HIROSE-ZX62R-B-5P
J2: 01x08; Pin_Header_Straight_2x04_Pitch2.54mm
J3: 02x03; Pin_Header_Straight_2x03_Pitch2.54mm
J4: 01x03; Pin_Header_Straight_1x03_Pitch2.54mm
J5: 01x06; Pin_Header_Straight_1x06_Pitch2.54mm
R1: 1M; R_0603_HandSoldering
R2: 0.05; C_Disc_D4.3mm_W1.9mm_P5.00mm
R3: 1K; R_0603_HandSoldering
R4, R5, R6: 470; R_0603_HandSoldering
TP1: WAKEUP; Pin_Header_Straight_1x01_Pitch2.54mm
U1: CP2102N; SiliconLabs_QFN-20-1EP_3x3mm_Pitch0.5mm_ThermalVias
U2: NJU7223DL1-33; TO-252-2

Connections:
+3V3: C7.2, J4.3, U2.1
+5V: C1.2, C3.2, C6.2, J2.1, J4.1, R2.1, U1.7, U1.8, U2.2
CTS: J3.6, J5.6, U1.15
GND: C1.1, C2.2, C3.1, C4.1, C5.1, C6.1, C7.1, D1.2, D2.2, D3.1, D4.1, D5.1, J1.5, J3.3, J5.3, R1.2, U1.3, U1.12, U1.21, U2.3
unnamed: C2.1, J1.6, R1.1
unnamed: D1.1, J1.2, U1.5
unnamed: D2.1, J1.3, U1.4
unnamed: D3.2, R4.2
unnamed: D4.2, R5.2
unnamed: D5.2, R6.2
unnamed: J1.1, R2.2
unnamed: J2.3, U1.14
unnamed: J2.4, R4.1, U1.11
unnamed: J2.5, U1.2
unnamed: J2.6, U1.1
unnamed: J3.4, J4.2, J5.4
unnamed: R3.1, U1.9
unnamed: TP1.1, U1.13
RTS: J3.5, J5.5, U1.16
RXD: J3.1, J5.1, U1.17
RXT: J2.8, R6.1, U1.19
TXD: J3.2, J5.2, U1.18
TXT: J2.7, R5.1, U1.20
VDD: C4.2, C5.2, J2.2, R3.2, U1.6
